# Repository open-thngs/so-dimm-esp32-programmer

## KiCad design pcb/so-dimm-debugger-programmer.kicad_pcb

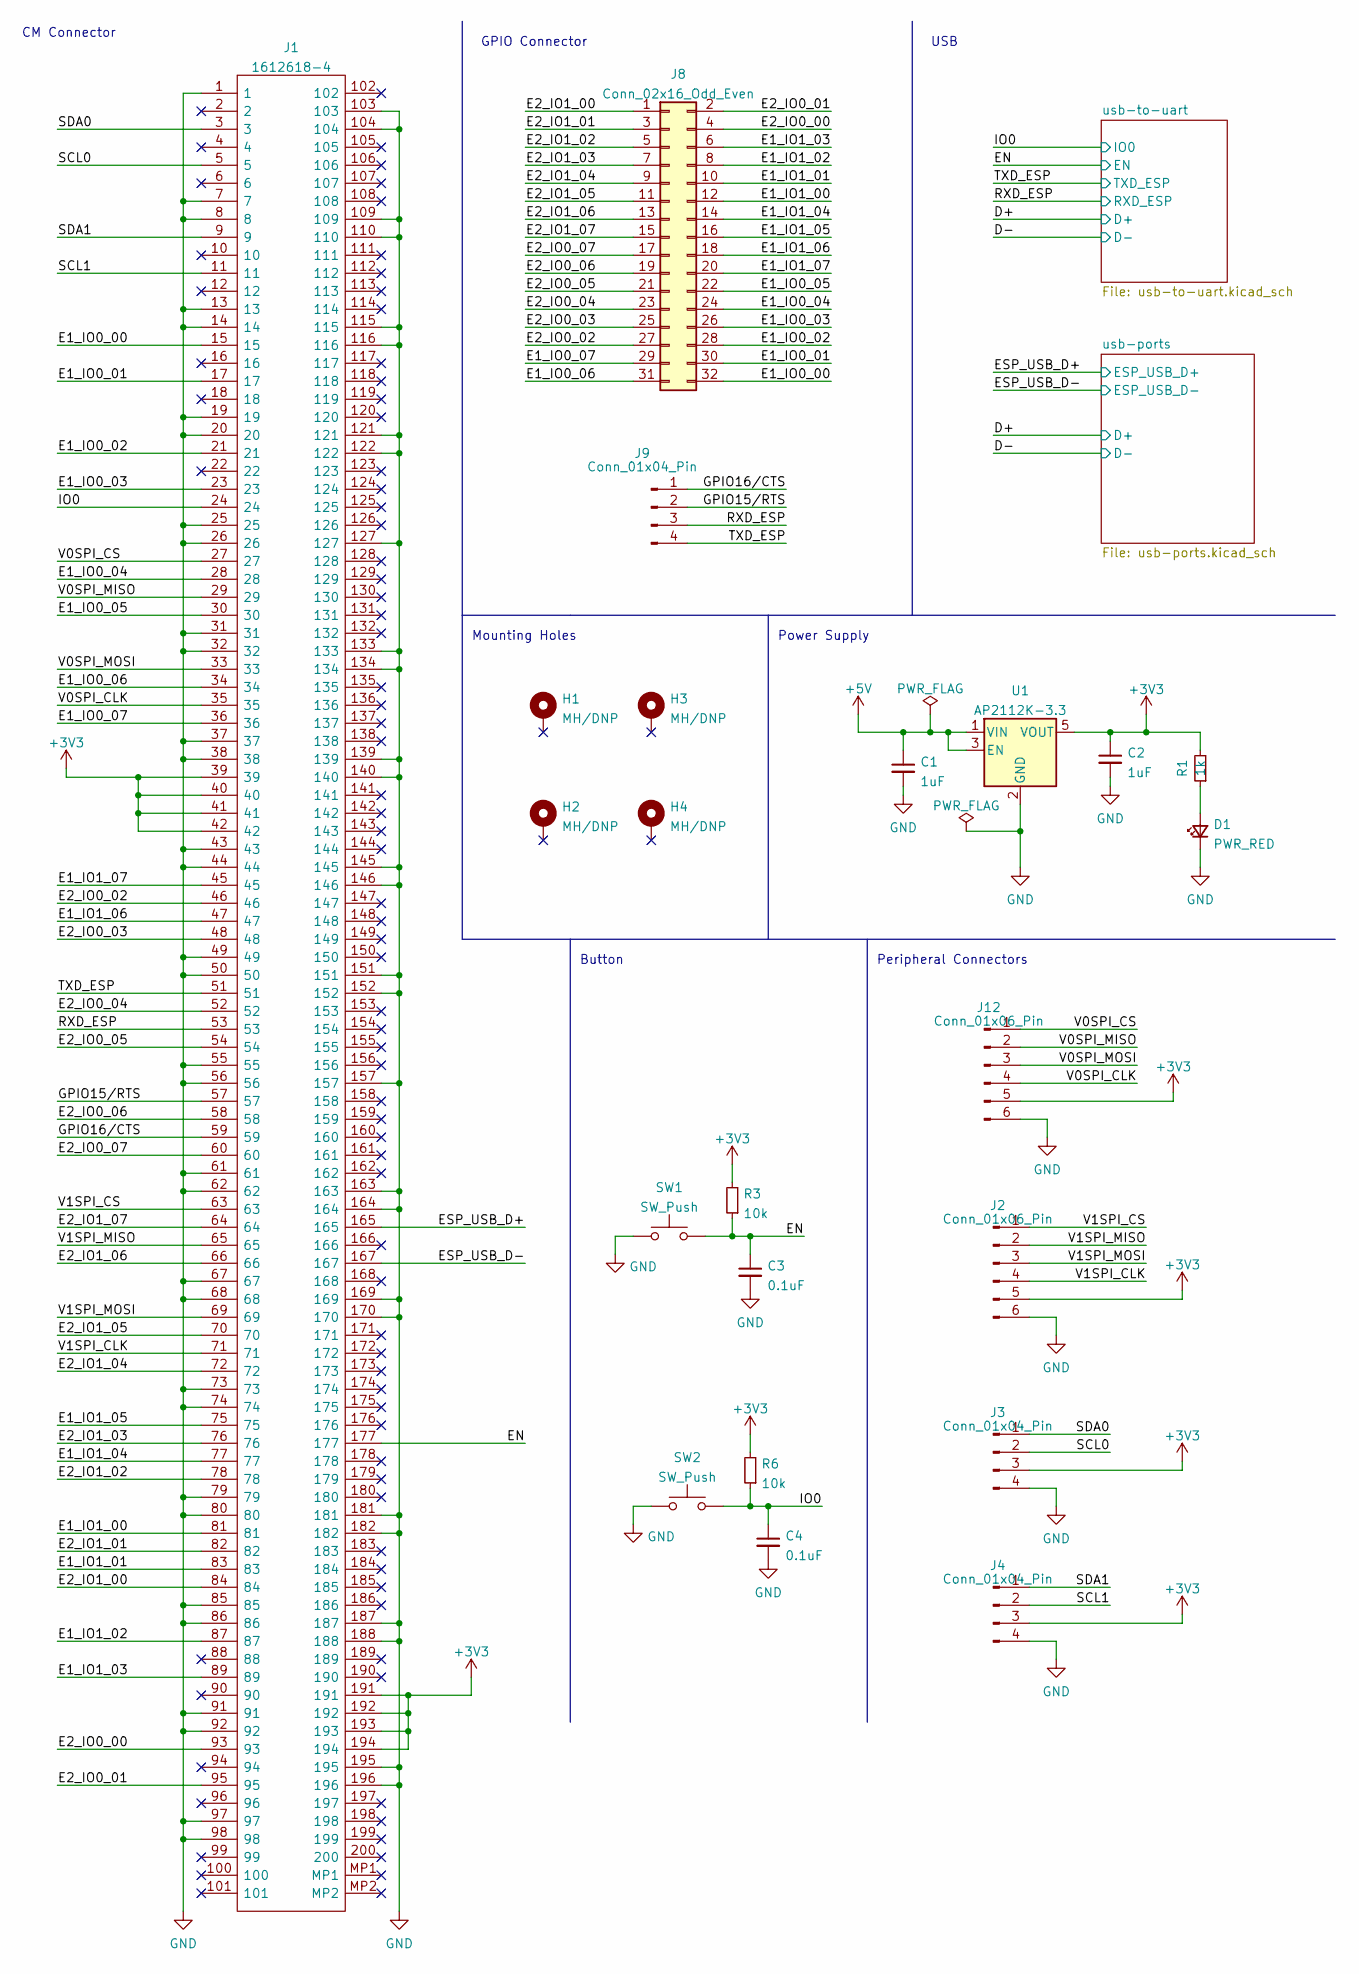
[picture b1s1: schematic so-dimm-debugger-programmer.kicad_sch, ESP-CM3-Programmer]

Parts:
C1, C2: 1uF; C_0603_1608Metric
C3, C4: 0.1uF; C_0603_1608Metric
D1: PWR_RED; LED_0603_1608Metric
H1, H2, H3, H4: MH/DNP; MountingHole_2.5mm_Pad_Via
J1: 1612618-4; 16126184; Manufacturer_Part_Number 1612618-4; Mouser Part Number 571-1612618-4
J2, J12: Conn_01x06_Pin; PinHeader_1x06_P2.54mm_Vertical
J3, J4, J9: Conn_01x04_Pin; PinHeader_1x04_P2.54mm_Vertical
J8: Conn_02x16_Odd_Even; PinHeader_2x16_P2.54mm_Vertical
R1: 1k; R_0603_1608Metric
R3, R6: 10k; R_0603_1608Metric
SW1, SW2: SW_Push; SKRKAEE020
U1: AP2112K-3.3; SOT-23-5

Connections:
+3V3: C2.1, J1.39, J1.40, J1.41, J1.42, J1.191, J1.192, J1.193, J1.194, J2.5, J3.3, J4.3, J12.5, R1.2, R3.2, R6.2, U1.5 (VOUT); also elsewhere on the board
+5V: C1.1, U1.1 (VIN), U1.3 (EN); also elsewhere on the board
/E1_IO0_00: J1.15, J8.32
/E1_IO0_01: J1.17, J8.30
/E1_IO0_02: J1.21, J8.28
/E1_IO0_03: J1.23, J8.26
/E1_IO0_04: J1.28, J8.24
/E1_IO0_05: J1.30, J8.22
/E1_IO0_06: J1.34, J8.31
/E1_IO0_07: J1.36, J8.29
/E1_IO1_00: J1.81, J8.12
/E1_IO1_01: J1.83, J8.10
/E1_IO1_02: J1.87, J8.8
/E1_IO1_03: J1.89, J8.6
/E1_IO1_04: J1.77, J8.14
/E1_IO1_05: J1.75, J8.16
/E1_IO1_06: J1.47, J8.18
/E1_IO1_07: J1.45, J8.20
/E2_IO0_00: J1.93, J8.4
/E2_IO0_01: J1.95, J8.2
/E2_IO0_02: J1.46, J8.27
/E2_IO0_03: J1.48, J8.25
/E2_IO0_04: J1.52, J8.23
/E2_IO0_05: J1.54, J8.21
/E2_IO0_06: J1.58, J8.19
/E2_IO0_07: J1.60, J8.17
/E2_IO1_00: J1.84, J8.1
/E2_IO1_01: J1.82, J8.3
/E2_IO1_02: J1.78, J8.5
/E2_IO1_03: J1.76, J8.7
/E2_IO1_04: J1.72, J8.9
/E2_IO1_05: J1.70, J8.11
/E2_IO1_06: J1.66, J8.13
/E2_IO1_07: J1.64, J8.15
/EN: C3.1, J1.177, R3.1, SW1.2; also elsewhere on the board
/ESP_USB_D+: J1.165; also elsewhere on the board
/ESP_USB_D-: J1.167; also elsewhere on the board
/GPIO15/RTS: J1.57, J9.2
/GPIO16/CTS: J1.59, J9.1
/IO0: C4.1, J1.24, R6.1, SW2.2; also elsewhere on the board
/RXD_ESP: J1.53, J9.3; also elsewhere on the board
/SCL0: J1.5, J3.2
/SCL1: J1.11, J4.2
/SDA0: J1.3, J3.1
/SDA1: J1.9, J4.1
/TXD_ESP: J1.51, J9.4; also elsewhere on the board
/V0SPI_CLK: J1.35, J12.4
/V0SPI_CS: J1.27, J12.1
/V0SPI_MISO: J1.29, J12.2
/V0SPI_MOSI: J1.33, J12.3
/V1SPI_CLK: J1.71, J2.4
/V1SPI_CS: J1.63, J2.1
/V1SPI_MISO: J1.65, J2.2
/V1SPI_MOSI: J1.69, J2.3
GND: C1.2, C2.2, C3.2, C4.2, D1.1 (K), J1.1, J1.7, J1.8, J1.13, J1.14, J1.19, J1.20, J1.25, J1.26, J1.31, J1.32, J1.37, J1.38, J1.43, J1.44, J1.49, J1.50, J1.55, J1.56, J1.61, J1.62, J1.67, J1.68, J1.73, J1.74, J1.79, J1.80, J1.85, J1.86, J1.91, J1.92, J1.97, J1.98, J1.103, J1.104, J1.109, J1.110, J1.115, J1.116, J1.121, J1.122, J1.127, J1.133, J1.134, J1.139, J1.140, J1.145, J1.146, J1.151, J1.152, J1.157, J1.163, J1.164, J1.169, J1.170, J1.181, J1.182, J1.187, J1.188, J1.195, J1.196, J2.6, J3.4, J4.4, J12.6, SW1.1, SW2.1, U1.2 (GND); also elsewhere on the board
unnamed: D1.2 (A), R1.1

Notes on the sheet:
Mounting Holes
CM Connector
USB
GPIO Connector
Peripheral Connectors
Button
Power Supply

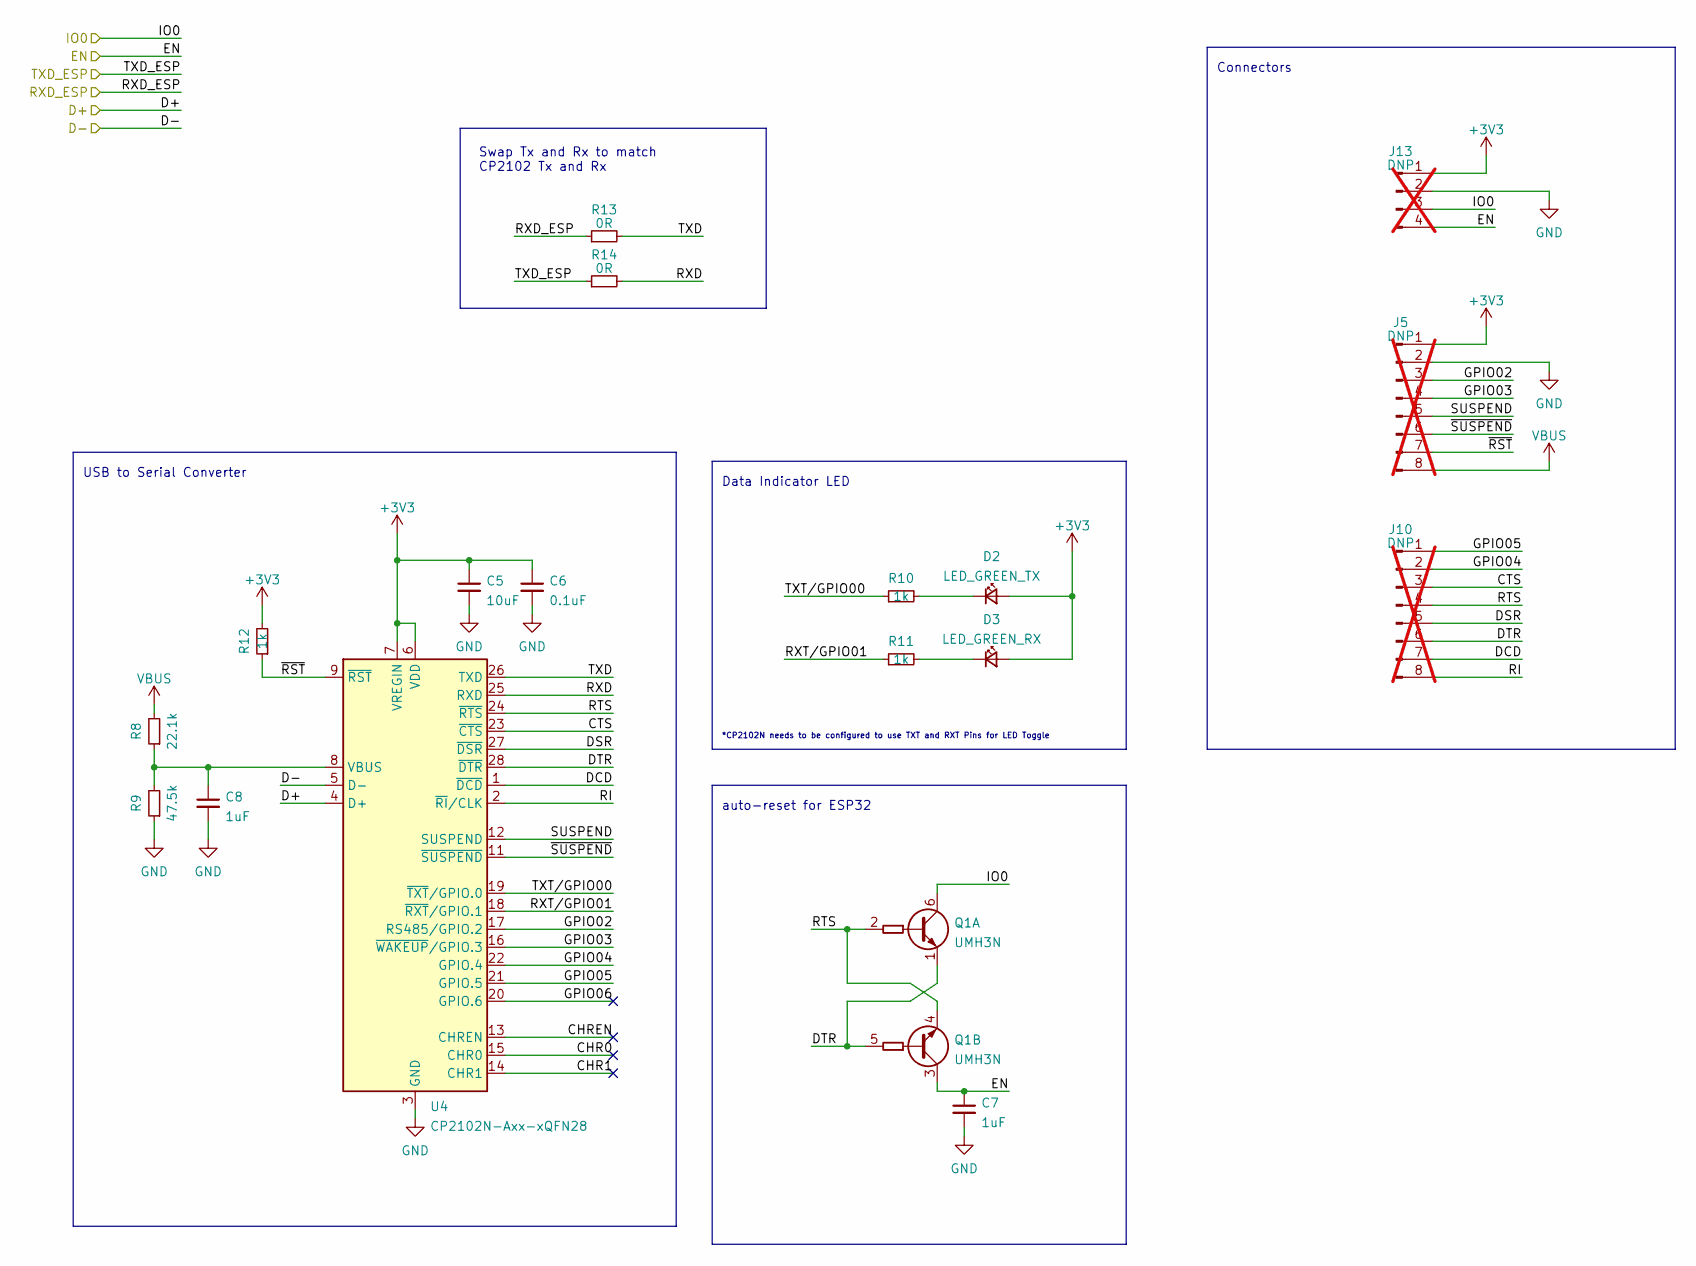
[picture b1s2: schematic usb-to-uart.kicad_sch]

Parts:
C5: 10uF; C_0603_1608Metric
C6: 0.1uF; C_0603_1608Metric
C7, C8: 1uF; C_0603_1608Metric
D2: LED_GREEN_TX; LED_0603_1608Metric
D3: LED_GREEN_RX; LED_0603_1608Metric
J5, J10: DNP; PinHeader_1x08_P2.54mm_Vertical; not fitted
J13: DNP; PinHeader_1x04_P2.54mm_Vertical; not fitted
Q1: UMH3N; SOT-363_SC-70-6
R8: 22.1k; R_0603_1608Metric
R9: 47.5k; R_0603_1608Metric
R10, R11, R12: 1k; R_0603_1608Metric
R13, R14: 0R; R_0603_1608Metric
U4: CP2102N-Axx-xQFN28; QFN-28-1EP_5x5mm_P0.5mm_EP3.35x3.35mm

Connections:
+3V3: C5.1, C6.1, D2.2 (A), D3.2 (A), J5.1, J13.1, R12.2, U4.6 (VDD), U4.7 (VREGIN); also elsewhere on the board
/D+: U4.4 (D+); also elsewhere on the board
/D-: U4.5 (D-); also elsewhere on the board
/EN: C7.1, J13.4, Q1.3 (C2); also elsewhere on the board
/IO0: J13.3, Q1.6 (C1); also elsewhere on the board
/RXD_ESP: R13.1; also elsewhere on the board
/TXD_ESP: R14.1; also elsewhere on the board
/usb-to-uart/CHR0: U4.15 (CHR0)
/usb-to-uart/CHR1: U4.14 (CHR1)
/usb-to-uart/CHREN: U4.13 (CHREN)
/usb-to-uart/CTS: J10.3, U4.23 (~CTS)
/usb-to-uart/DCD: J10.7, U4.1 (~DCD)
/usb-to-uart/DSR: J10.5, U4.27 (~DSR)
/usb-to-uart/DTR: J10.6, Q1.1 (E1), Q1.5 (B2), U4.28 (~DTR)
/usb-to-uart/GPIO02: J5.3, U4.17 (RS485/GPIO.2)
/usb-to-uart/GPIO03: J5.4, U4.16 (~WAKEUP/GPIO.3)
/usb-to-uart/GPIO04: J10.2, U4.22 (GPIO.4)
/usb-to-uart/GPIO05: J10.1, U4.21 (GPIO.5)
/usb-to-uart/GPIO06: U4.20 (GPIO.6)
/usb-to-uart/RI: J10.8, U4.2 (~RI/CLK)
/usb-to-uart/RTS: J10.4, Q1.2 (B1), Q1.4 (E2), U4.24 (~RTS)
/usb-to-uart/RXD: R14.2, U4.25 (RXD)
/usb-to-uart/RXT/GPIO01: R11.1, U4.18 (~RXT/GPIO.1)
/usb-to-uart/SUSPEND: J5.5, U4.12 (SUSPEND)
/usb-to-uart/TXD: R13.2, U4.26 (TXD)
/usb-to-uart/TXT/GPIO00: R10.1, U4.19 (~TXT/GPIO.0)
/usb-to-uart/~RST: J5.7, R12.1, U4.9 (~RST)
/usb-to-uart/~SUSPEND: J5.6, U4.11 (~SUSPEND)
GND: C5.2, C6.2, C7.2, C8.2, J5.2, J13.2, R9.1, U4.3 (GND), U4.29 (GND); also elsewhere on the board
unnamed: D2.1 (K), R10.2
unnamed: D3.1 (K), R11.2
unnamed: C8.1, R8.1, R9.2, U4.8 (VBUS)
VBUS: J5.8, R8.2; also elsewhere on the board

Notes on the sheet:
Swap Tx and Rx to match CP2102 Tx and Rx
Connectors
USB to Serial Converter
*CP2102N needs to be configured to use TXT and RXT Pins for LED Toggle
Data Indicator LED
auto-reset for ESP32

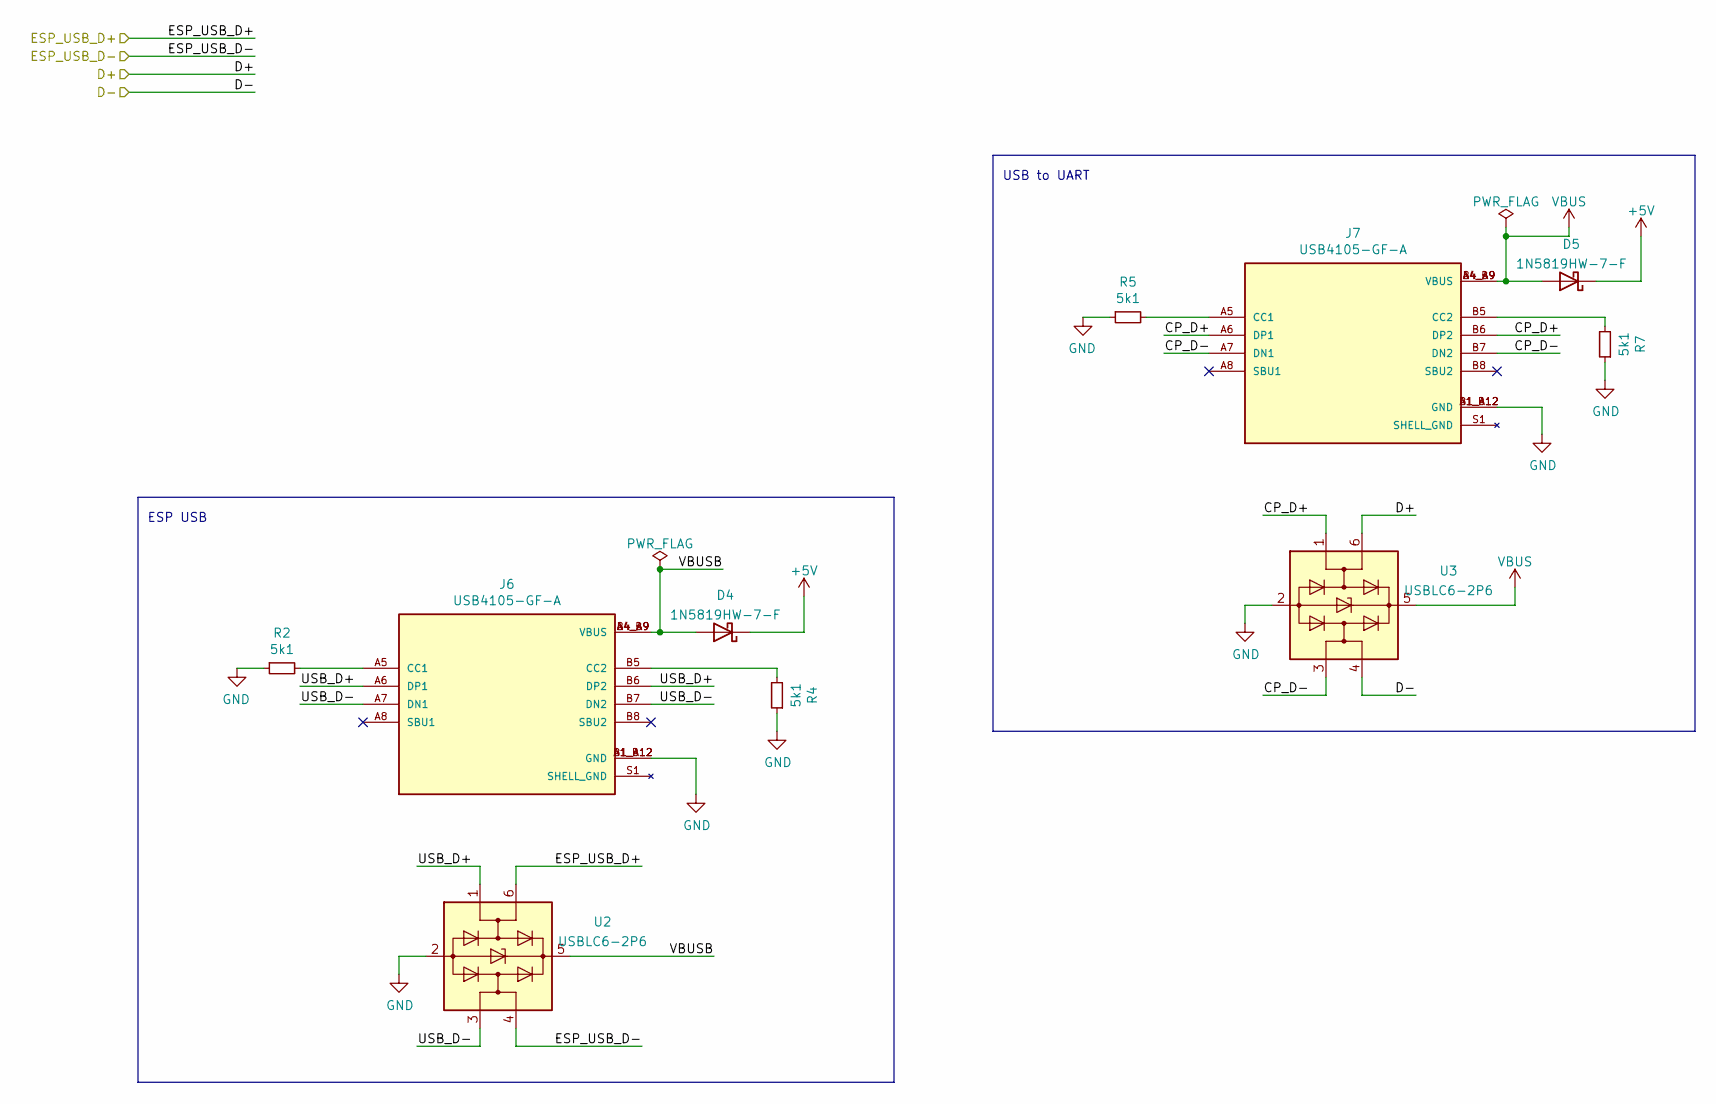
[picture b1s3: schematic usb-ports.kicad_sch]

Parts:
D4, D5: 1N5819HW-7-F; D_SOD-123
J6, J7: USB4105-GF-A; GCT_USB4105-GF-A; PARTREV A3
R2, R4, R5, R7: 5k1; R_0603_1608Metric
U2, U3: USBLC6-2P6; SOT-666

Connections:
+5V: D4.1 (K), D5.1 (K); also elsewhere on the board
/D+: U3.6 (I/O1); also elsewhere on the board
/D-: U3.4 (I/O2); also elsewhere on the board
/ESP_USB_D+: U2.6 (I/O1); also elsewhere on the board
/ESP_USB_D-: U2.4 (I/O2); also elsewhere on the board
/usb-ports/CP_D+: J7.A6 (DP1), J7.B6 (DP2), U3.1 (I/O1)
/usb-ports/CP_D-: J7.A7 (DN1), J7.B7 (DN2), U3.3 (I/O2)
/usb-ports/USB_D+: J6.A6 (DP1), J6.B6 (DP2), U2.1 (I/O1)
/usb-ports/USB_D-: J6.A7 (DN1), J6.B7 (DN2), U2.3 (I/O2)
/usb-ports/VBUSB: D4.2 (A), J6.A4_B9 (VBUS), J6.B4_A9 (VBUS), U2.5 (VBUS)
GND: J6.A1_B12 (GND), J6.B1_A12 (GND), J7.A1_B12 (GND), J7.B1_A12 (GND), R2.1, R4.1, R5.1, R7.1, U2.2 (GND), U3.2 (GND); also elsewhere on the board
unnamed: J6.A5 (CC1), R2.2
unnamed: J6.B5 (CC2), R4.2
unnamed: J7.A5 (CC1), R5.2
unnamed: J7.B5 (CC2), R7.2
VBUS: D5.2 (A), J7.A4_B9 (VBUS), J7.B4_A9 (VBUS), U3.5 (VBUS); also elsewhere on the board

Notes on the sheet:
ESP USB
USB to UART

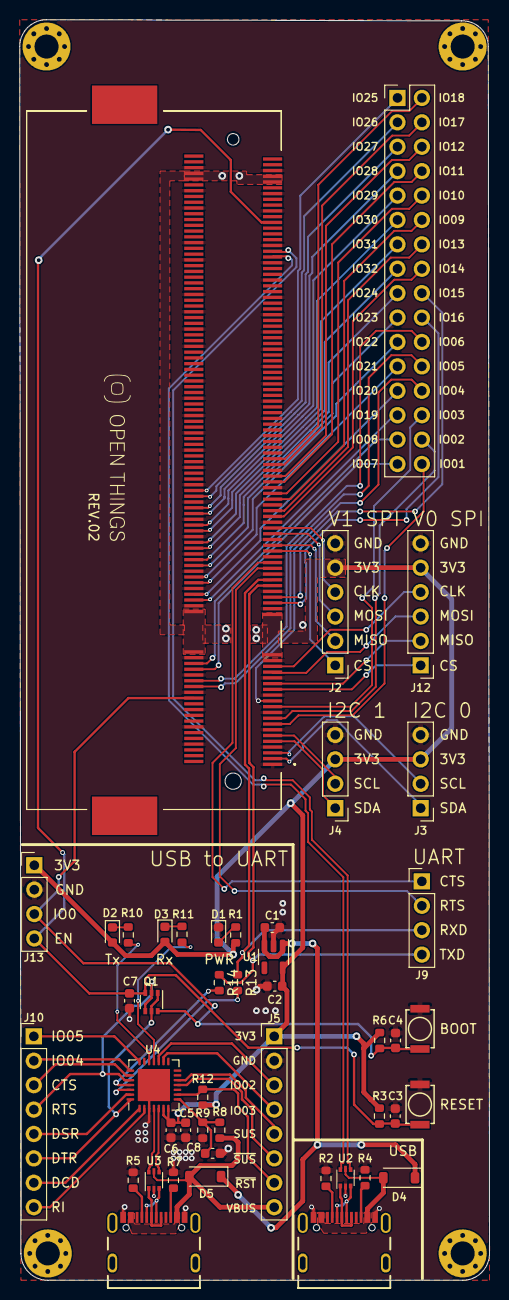
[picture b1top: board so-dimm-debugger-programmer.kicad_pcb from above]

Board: 2 copper layers, 48.9 x 131.2 mm, 51 parts (0 on the bottom side), 88 nets.

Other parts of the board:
G1: LOGO

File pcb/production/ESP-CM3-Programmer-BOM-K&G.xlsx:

|  |  | Kunde: | Mirko Häberlin - open-things
 |  |  | Projektname: | Openthing 1 - ESP-CM3
 |  |  | Menge: | 20, 100
 | KRÜGER & GOTHE GMBH
 | electronic products and services
 | Atzendorfer Str. 19 • 39418 Staßfurt
 | www.kug-ems.de
Pos. | CPN interne Kundenartikelnummer costumer part number | Beschreibung Artikelparameter describtion | Referenzen credentials | T/B | Menge Quantity | MPN Herstellerteilenummer manufacturer part number | Hersteller Manufacturer | MPN Alternative 1 | Hersteller Alternative 1 | MPN Alternative 2 | Hersteller Alternative 2 | Bemerkung
0001 |  | Capacitor 1µF 0603 | C1, C2, C7, C8 | T | 4.0 | 1uF
0002 |  | Capacitor 0.1µF 0603 | C3, C4, C6 | T | 3.0 | 0.1uF
0003 |  | Capacitor 10µF 0603 | C5 | T | 1.0 | 10uF
0004 |  | LED Rot 0603 | D1 | T | 1.0 | LED RED
0005 |  | 603.0 | D2 | T | 1.0 | LED GREEN TX
0006 |  | 603.0 | D3 | T | 1.0 | LED GREEN RX
0007 |  | SCHOTTKY Diode SOD-123 | D4, D5 | T | 2.0 | 1N5819HW-7-F
0008 |  | DDR2-SO-DIMM-Sockel | J1 | T | 1.0 | 1612618-4 | TE Connectivity
0009 |  | PinHeader_1x06_P2.54mm_Vertical | J12, J2 | T | 2.0 | Conn_01x06_Pin
0010 |  | PinHeader_1x04_P2.54mm_Vertical | J3, J4, J9 | T | 3.0 | Conn_01x04_Pin
0011 |  | GCT_USB4105-GF-A | J6, J7 | T | 2.0 | USB4105-GF-A | Global Connector Technology (GCT) | TYPE-C-31-M-12 | Korean Hroparts Elec
0012 |  | PinHeader_2x16_P2.54mm_Vertical | J8 | T | 1.0 | Conn_02x16_Odd_Even
0013 |  | NPN+NPN-Digitaltransistor SOT-363_SC-70-6 | Q1 | T | 1.0 | UMH3N | ROHM Semiconductor
0014 |  | Widerstand 1k 0603 | R1, R10, R11, R12 | T | 4.0 | 1k
0015 |  | Widerstand 0R 0603 | R13, R14 | T | 2.0 | 0R
0016 |  | Widerstand 5.1k 0603 | R2, R4, R5, R7 | T | 4.0 | 5k1
0017 |  | Widerstand 10k 0603 | R3, R6 | T | 2.0 | 10k
0018 |  | Widerstand 22.1k 0603 | R8 | T | 1.0 | 22.1k
0019 |  | Widerstand 47.5k 0603 | R9 | T | 1.0 | 47.5k
0020 |  | Sensorschalter 3.9x2.9x2.0mm 160gf SKRKAEE020 | SW1, SW2 | T | 2.0 | SKRKAEE020 | Alps Alpine
0021 |  | LDO Spannungs-Regulator 600mA CMOS LDO 50mA 3.3V 250mV SOT-23-5 | U1 | T | 1.0 | AP2112K-3.3 | Diodes Incorporated
0022 |  | ESD-Entstörer/TVS-Dioden High Speed Interface Protection Low Cap SOT-666 | U2, U3 | T | 2.0 | USBLC6-2P6 | STMicroelectronics
0023 |  | USB-IC-Schnittstelle USBXpress - USB to UART Bridge QFN-28-1EP_5x5mm_P0.5mm_EP3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 | U4 | T | 1.0 | CP2102N-Axx-xQFN28 | Silicon Labs
0024
0025

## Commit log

2023-03-27 Add inital esp32 programmer pcb data
2023-03-31 Added first version of the pcb layout
2023-03-31 Finished up board layout
2023-03-31 Try to fix all ERC and DRC Issues and Warning + changed violation config
2023-04-03 Small PCB silk adjustments
2023-04-05 Test quick-start workflow from kibot
2023-04-05 update cache after installing font
2023-04-05 Added font to the resources for KiBot
2023-04-05 Removed download and install of font from kicad action for kibot
2023-04-17 Add font license
2023-04-17 Added dependency that DRC needs to wait for ERC
2023-04-17 Try out quick start of KiBot
2023-04-17 Go back to custom KiBot actions
2023-06-23 Fixed Rx Tx not being swapped between CP2102 and ESP-CM3 connector
    + Fix Label for PWR and Rx (swapped)
2023-09-08 Modified 3D objects
2023-09-08 Applied latest KiBot action to project
2023-09-08 Ignore SPICE issues
2023-09-12 Fix E1_IO0_3 connected to Pin 22 instead of 23
2023-09-13 Fix font issue with KiCad returning to default font
2023-09-13 Fix unconnected plane
2023-09-21 Changed cfg to export pick and place as CSV
2023-09-29 Removed unpopulated pin header from BOM
2023-09-29 Added revision silk to top layer
2023-09-29 Added date and revision to schematic
2023-10-09 Fix copper to edge issue
2023-10-09 Change copper to edge clearance from 0.025 to 0.25
2023-10-20 Enabled designators for terminal connectors
2023-10-20 Change silk-text size for terminal connectors from 0.6 to 0.8
2023-10-20 Fixed thermal reliefe count for serveral pads
2024-03-15 ignore lck files
2024-03-15 Changed excludes from BOM
2024-03-21 Added generated data
2024-03-21 Set USB Ports to be TH instead of SMD
2024-11-06 Add production files specification and board dimensions
2024-11-06 small pcb changes?
2024-12-09 Add workflow_dispatch to kibot.yml action
